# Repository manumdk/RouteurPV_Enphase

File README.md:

# RouteurPV_Enphase
Routeur PV Enphase Esp32

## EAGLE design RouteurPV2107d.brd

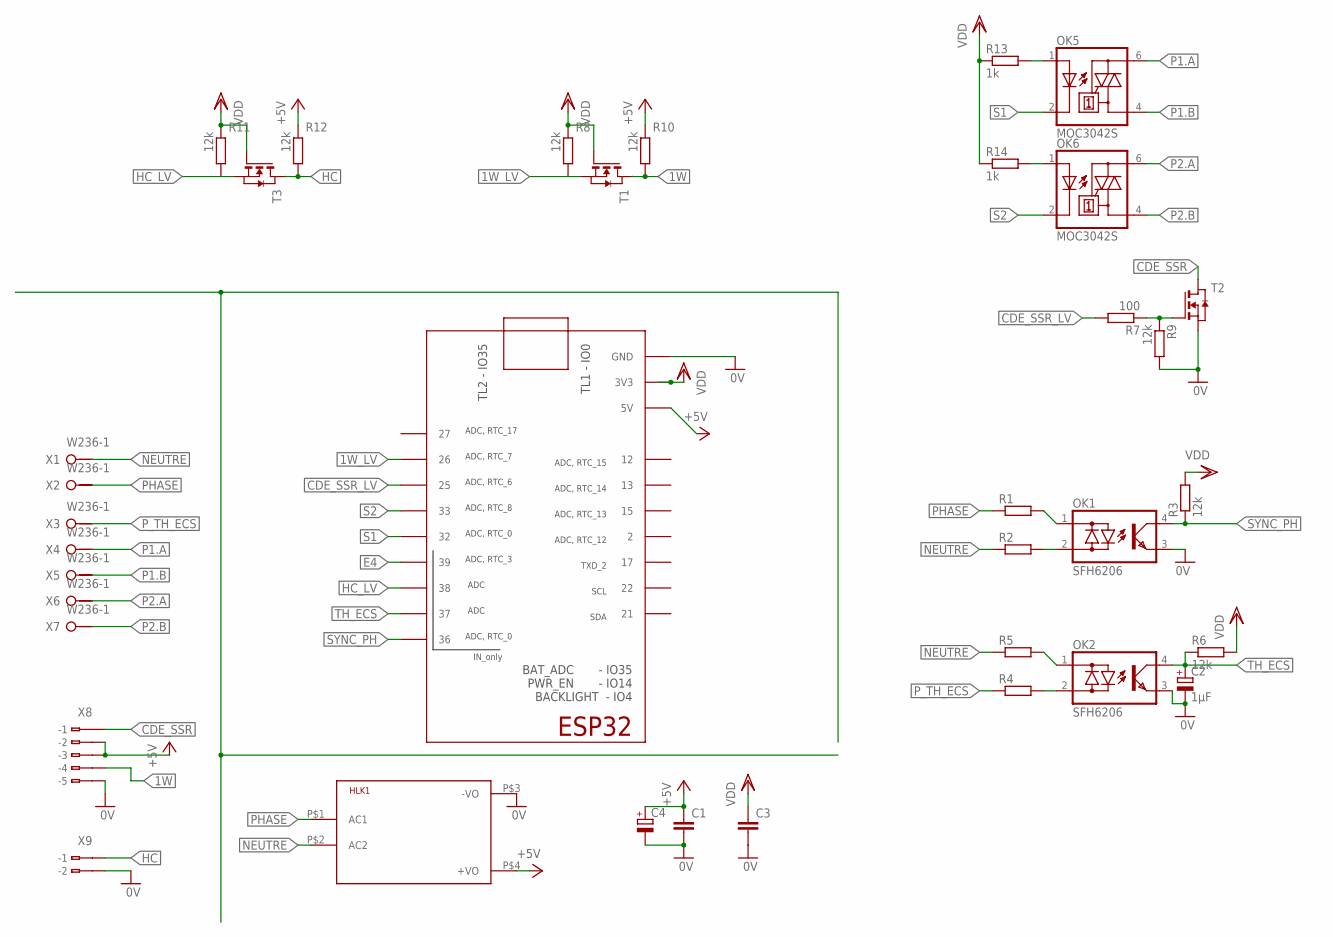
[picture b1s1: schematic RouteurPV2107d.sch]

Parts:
C1, C3: C-EUC1206; C1206
C2: 1µF; R/2012-12R
C4: CPOL-EUSMCC; SMC_C
HLK1: HLK-PM013W; HLK-PM01
IC1: TTGO_DISP; TTGO_DISP_DEFAULT
OK1, OK2: SFH6206; DIL4-SMD
OK5, OK6: MOC3042S; DIL6-SMD
R1, R2, R4, R5: R-EU_R2512; R2512
R3, R6, R8, R9, R10, R11, R12: 12k; R1206
R7: 100; R1206
R13, R14: 1k; R1206
T1, T2, T3: NMOSSOT23; SOT-23
X1, X2, X3, X4, X5, X6, X7: W236-1
X8: 233-505
X9: 233-102

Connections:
0V: C1.2, C2.-, C3.2, C4.-, HLK1.P$3 (-VO), IC1.GND_1 (GND), IC1.GND_2 (GND), IC1.GND_3 (GND), IC1.GND_4 (GND), IC1.GND_5 (GND), OK1.3 (E), OK2.3 (E), R9.2, T2.2 (S), X8.B5 (B-5), X9.B2 (B-2)
1W: R10.2, T1.1 (D), X8.B4 (B-4)
1W_LV: IC1.26, R8.2, T1.2 (S)
+5V: C1.1, C4.+, HLK1.P$4 (+VO), IC1.5V, R10.1, R12.1, X8.B2 (B-2), X8.B3 (B-3)
CDE_SSR: T2.1 (D), X8.B1 (B-1)
CDE_SSR_LV: IC1.25, R7.2
E4: IC1.39
HC: R12.2, T3.1 (D), X9.B1 (B-1)
HC_LV: IC1.38, R11.2, T3.2 (S)
unnamed: OK1.1 (AC1), R1.2
unnamed: R7.1, R9.1, T2.3 (G)
unnamed: OK1.2 (AC2), R2.2
unnamed: OK2.2 (AC2), R4.2
unnamed: OK2.1 (AC1), R5.2
unnamed: OK5.1 (A), R13.2
unnamed: OK6.1 (A), R14.2
NEUTRE: HLK1.P$2 (AC2), R2.1, R5.1, X1.1 (KL1)
P1.A: OK5.6 (A2), X4.1 (KL1)
P1.B: OK5.4 (A1), X5.1 (KL1)
P2.A: OK6.6 (A2), X6.1 (KL1)
P2.B: OK6.4 (A1), X7.1 (KL1)
PHASE: HLK1.P$1 (AC1), R1.1, X2.1 (KL1)
P_TH_ECS: R4.1, X3.1 (KL1)
S1: IC1.32, OK5.2 (C)
S2: IC1.33, OK6.2 (C)
SYNC_PH: IC1.36, OK1.4 (C), R3.1
TH_ECS: C2.+, IC1.37, OK2.4 (C), R6.1
VDD: C3.1, IC1.3V3_1 (3V3), IC1.3V3_2 (3V3), R3.2, R6.2, R8.1, R11.1, R13.1, R14.1, T1.3 (G), T3.3 (G)

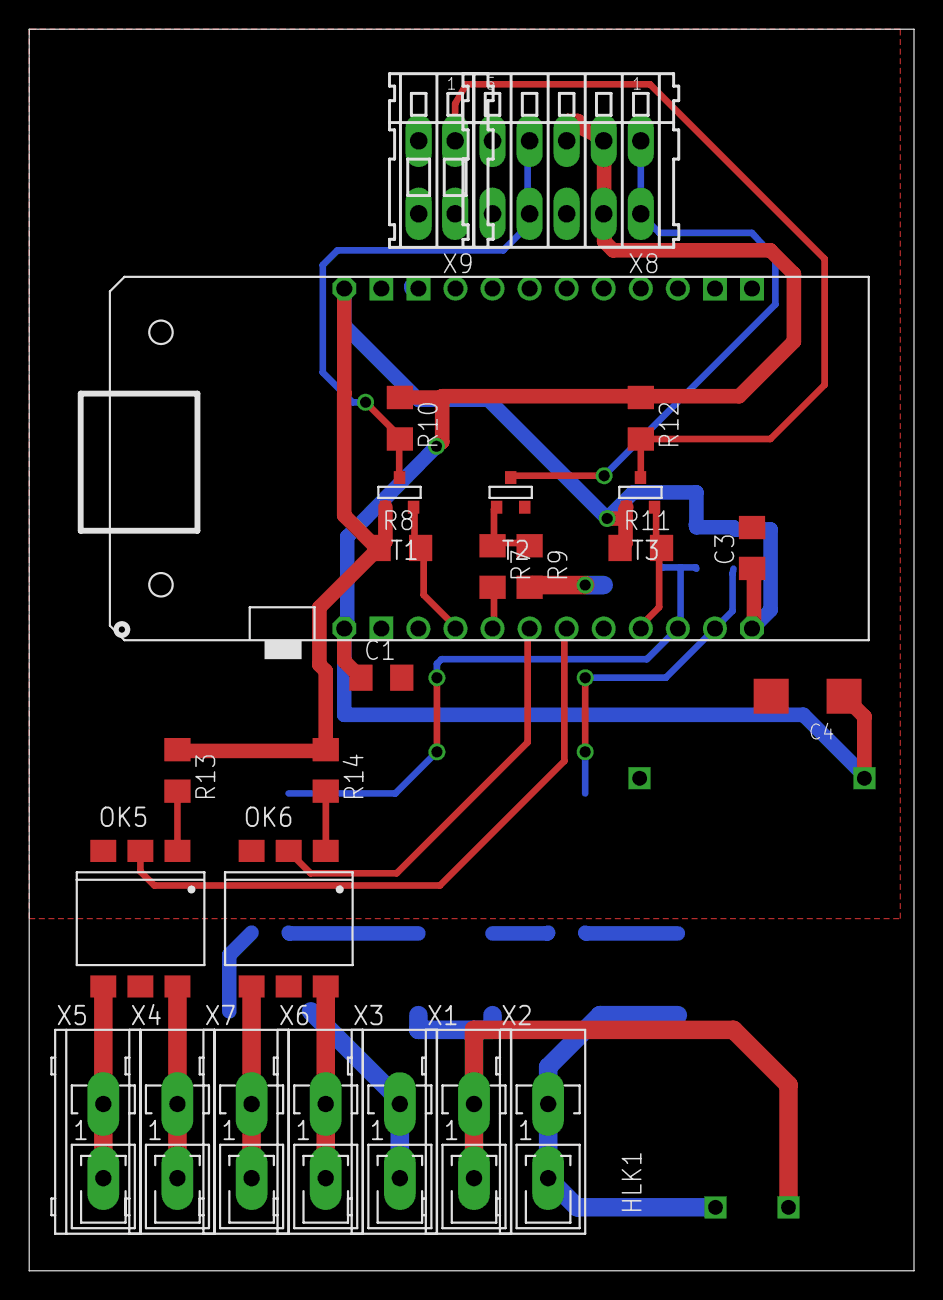
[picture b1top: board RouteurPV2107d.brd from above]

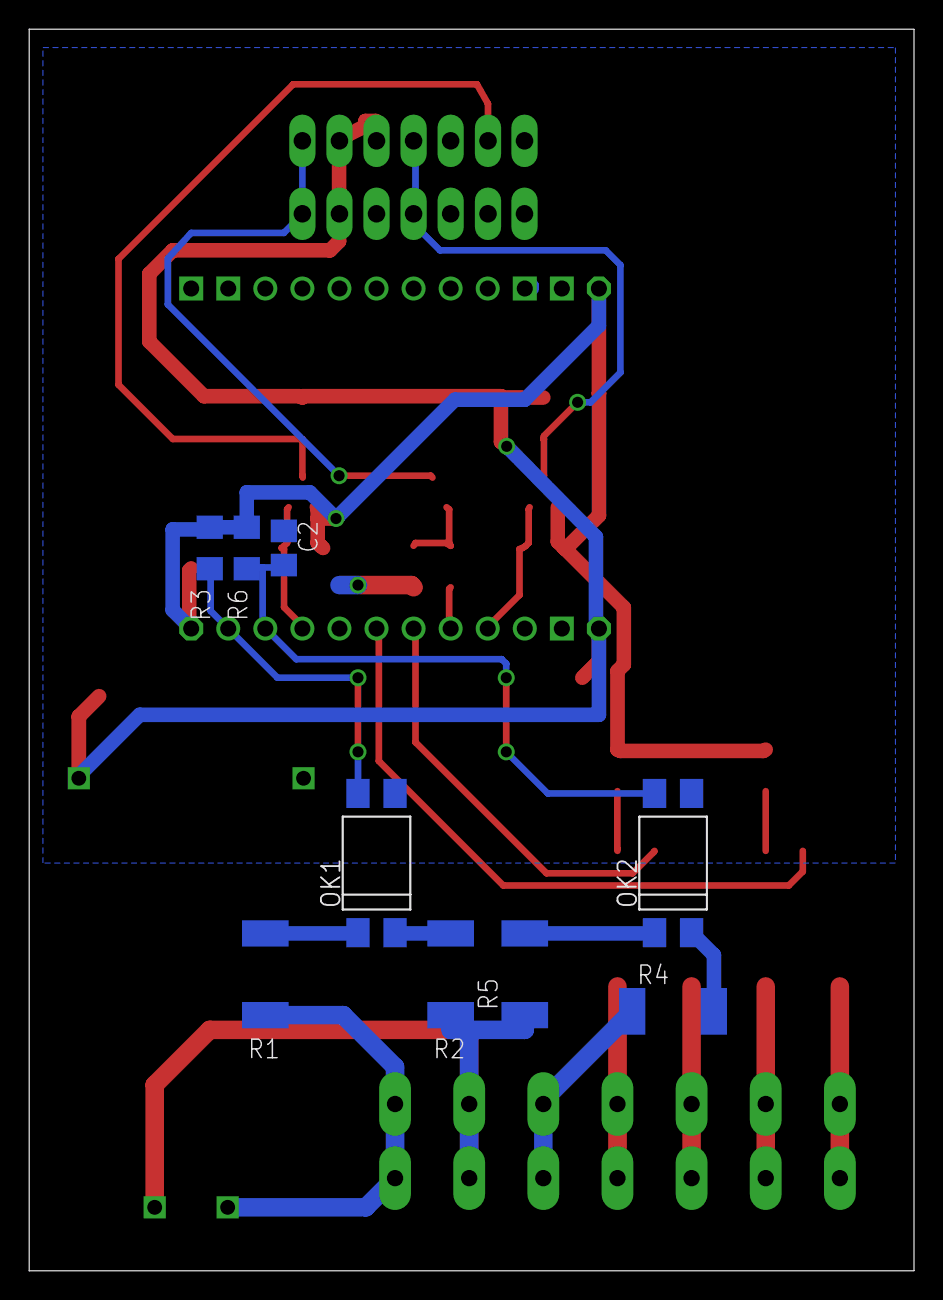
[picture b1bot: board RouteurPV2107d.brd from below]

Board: 2 copper layers, 60.6 x 85.1 mm, 36 parts (9 on the bottom side), 27 nets.

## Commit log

2021-07-27 readme.md
